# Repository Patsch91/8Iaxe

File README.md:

# 8]axe

The 8]axe is a 8-ASIC-BM1366 Miner based on the [0xaxe](https://github.com/shufps/0xaxe)

**rev1**: averaging at about 3.3-3,6TH/s with ~90 Watts on the wall on default settings (485Mhz) </br>
**rev2**: added boost converter to eliminate the extra 12V PSU / different design to fit vertain enclosures

**note**: The 8]axe is not a stand-alone device because it only supports USB. It can be run connected to a Raspberry Pi without problems. Also multiple devices can be connected to a single Pi. 

**WARNING**: The 8]Axe working with Voltage Domains is the end level boss for Pros. It's hard to get it working properly. The main reason is the powering scheme that uses 4 different voltage domain. It's difficult to get it into balance properly and needs very good and uniform cooling. The device works but can be super frustrating until it really is mining as it should. 
Therefore there is some WIP to eliminate the voltage-domains and chaining 8 Asics in one Domain instead. 
**There will be no further development in near future on this project by myself, due to another project *without* voltage-domains**
```

ASICs
=====

The 8]axe uses 8 ASICs of type BM1366

Compilation (Bootloader or CMSIS-DAP)
======================================
Start WSL on your PC and go through the followig steps:

```bash
# install curl
sudo apt install curl

# install rust
curl --proto '=https' --tlsv1.2 https://sh.rustup.rs -sSf | sh

# add to ~/.bash.rc (afterwards, opening a new terminal is needed)
echo 'source "$HOME/.cargo/env"' >> ~/.bashrc

# clone repository
git clone https://github.com/shufps/0xaxe

# clone submodules
cd 0xaxe
git submodule init
git submodule update

# add rust target for STM32L0 variants
rustup target add thumbv6m-none-eabi

# build firmware for L072
cd firmware/fw-L072KZ
./build.sh
```

## Using it on Windows running WSL

For windows the usbipd is needed to connect the device to WSL. Install it from here:

https://github.com/dorssel/usbipd-win/releases

Afterwards reboot your PC and open the `cmd` as Administrator.

Connect the USB to your PC and power on the 12V while pressing the BOOT Button to start the device in BOOT-Mode

Then:
```
C:\Windows\System32>usbipd list
Connected:
BUSID  VID:PID    DEVICE                                                        STATE
2-1    046d:c52b  Logitech USB Input Device, USB-Eingabegerät                   Not shared
3-1    0c76:161f  USB PnP Audio Device, USB-Eingabegerät                        Not shared
3-2    046d:c52b  Logitech USB Input Device, USB-Eingabegerät                   Not shared
3-3    046d:c548  Logitech USB Input Device, USB-Eingabegerät                   Not shared
4-1    8087:0aa7  Intel(R) Wireless Bluetooth(R)                                Not shared
4-2    2e8a:000c  Picoprobe CMSIS-DAP v2, Serielles USB-Gerät (COM3)            Attached
```

Note the `BUSID` for the STM32. Then

```
C:\Windows\System32> usbipd bind --busid 4-2
```

Afterwards start your WSL Linux

Then attach the device with:
```
C:\Windows\System32> usbipd attach --wsl --busid 4-2
```

When it is running you can check in your WSL-Linux if the probe is detected:
```
probe-rs list

The following debug probes were found:
[0]: Picoprobe CMSIS-DAP (VID: 2e8a, PID: 000c, Serial: E66138528337A532, CmsisDap)
```

Installation via USB Bootloader on board with `BOOT` button
===========================================================
The STM32L072CB variant has an integrated DFU Bootloader that starts when pressing the `BOOT` button during reset.

Afterwards the firmware can be flashed via `dfu-utils`:

```bash
# install cargo-binutils and llvm tools
cargo install cargo-binutils
rustup component add llvm-tools-preview

# create the firmware.bin
DEFMT_LOG=info cargo objcopy --release --bin qaxe -- -O binary 0xaxe.bin

# install dfu-utils
sudo apt-get install dfu-util

# after booting, list the devices
dfu-util --list

# flash the binary
dfu-util -a 0 -s 0x08000000:leave -D 0xaxe.bin
```

Config 
=============
Use the "config.yml.example" of the [Piaxe-Miner](https://github.com/shufps/piaxe-miner) and change it as follows:

```bash
debug_bm1366: false
verify_solo: false
miner: 0xaxe

# works only with public pool
#suggest_difficulty: 2048

0xaxe:
  name: 8]axe
  chips: 8
  fan_speed_1: 0.8
  asic_frequency: 480
  extranonce2_interval: 1.5
  serial_port_asic: "/dev/ttyACM0"
  serial_port_ctrl: "/dev/ttyACM1"

...
```

Mining Client
=============

Stratum Mining Client:<br>
https://github.com/shufps/piaxe-miner

Case
=============

I used a 80x160x170 aluminum case like this one: [Amazon](https://www.amazon.de/Aluminium-Projektbox-Mattschwarzer-DIY-Leiterplattenanschluss-W%C3%A4rmeableitungsgeh%C3%A4use-Bedienen/dp/B0CGGSVM8F/ref=sr_1_3?__mk_de_DE=%C3%85M%C3%85%C5%BD%C3%95%C3%91&crid=3NMRXLZY6ALUN&dib=eyJ2IjoiMSJ9.0MLZnspoRUt-5Sq-UXD83eHRPPewKvMh4lus8XXQpkgDJRroXYZdpFcvkPHZnSEZWGdyZPu25JsKw8C_Gw7j3U3yo7FGxp-UKuHRwNwGErpQnLGFtEGB8CJPhlUupGPSyBMCgfSQbhhh6rR9keuntOinXBiLTcwFkg9jAHzRan196B2bXwHWc_GQhccHhde_KeXf4lkzuWefDuMZS-GZUgLpMEkL2ri5-xO686sFxk3LH6hBDYjgFnlqzBNBpYp2-c1hxcX88ikJwDevu7zkgC_WFYcVderTFYBcHsyTKOc.TUGJK2RRMmqnw5Lux7s7qib6OQUQhYEMLp2vokTvp34&dib_tag=se&keywords=80x160x170+case&qid=1723150526&sprefix=80x160x170+case%2Caps%2C94&sr=8-3)

Added 2x80mm Noctua Fans to get it pretty silent 

Misc
====
If you like this project and want to support future work, feel free to donate to: (https://github.com/shufps/0xaxe)

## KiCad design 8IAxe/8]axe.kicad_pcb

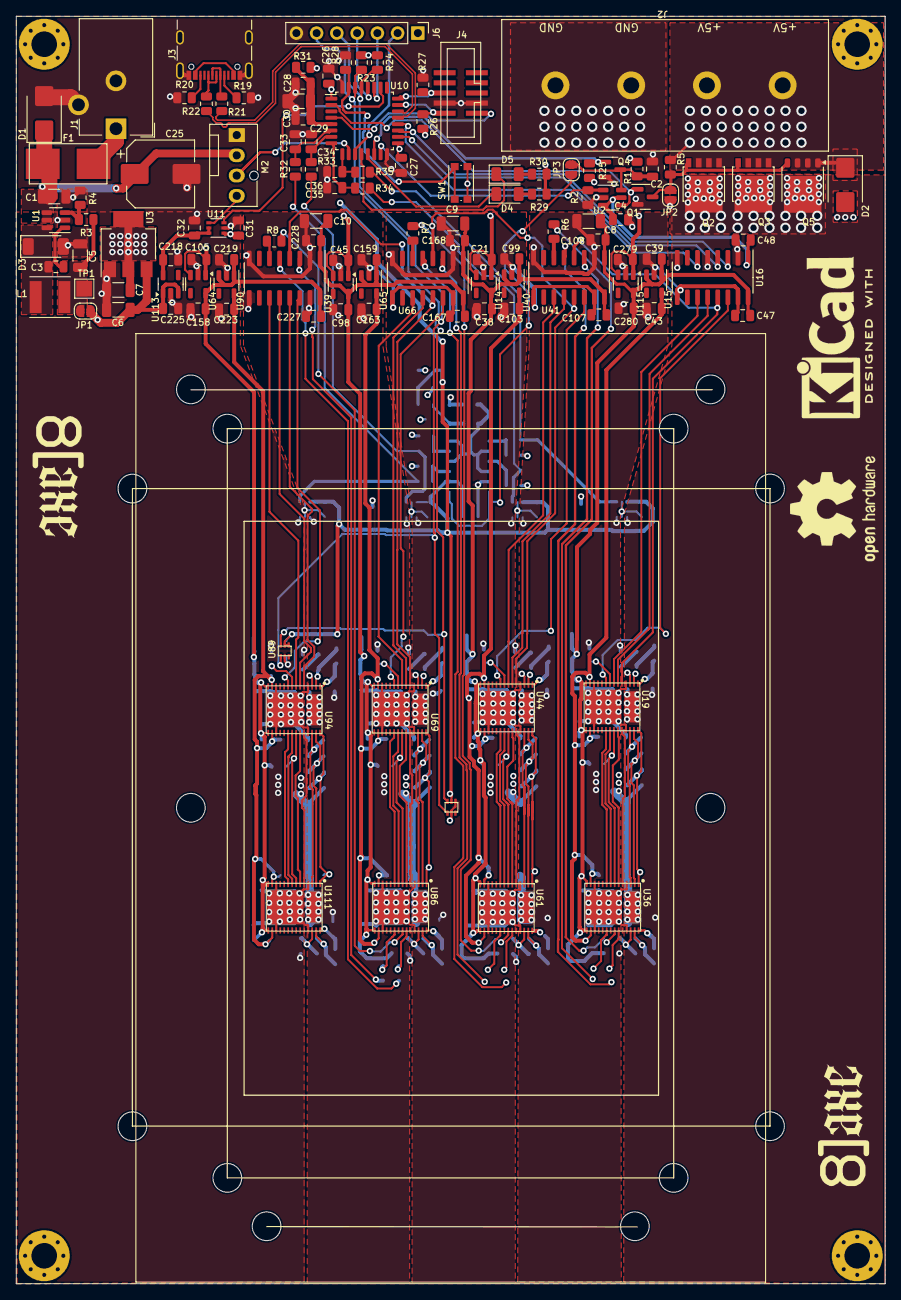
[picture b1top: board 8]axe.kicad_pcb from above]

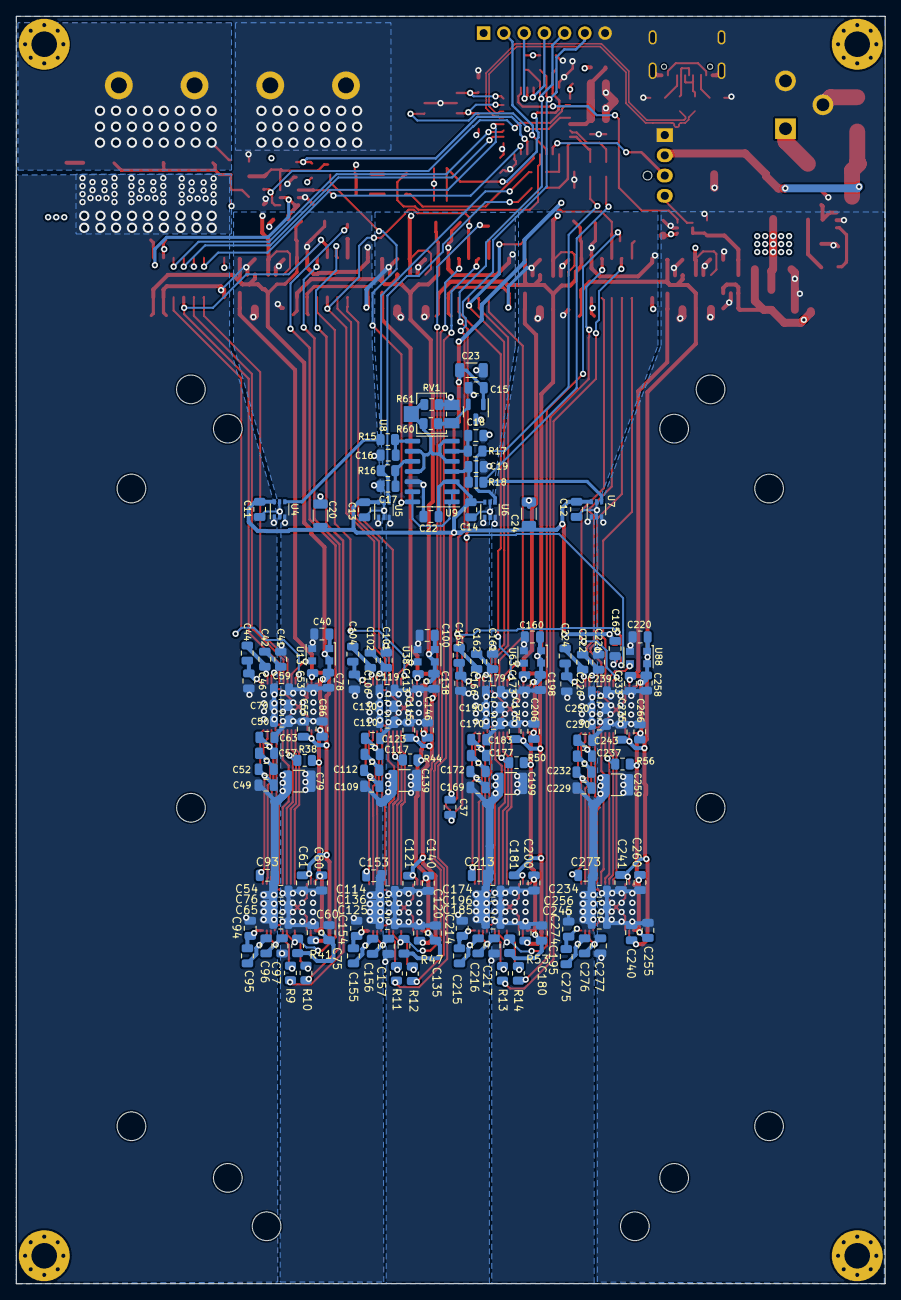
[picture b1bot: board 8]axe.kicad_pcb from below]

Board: 4 copper layers, 109.0 x 159.0 mm, 285 parts (161 on the bottom side), 164 nets.

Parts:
C1, C6, C8, C9, C10, C20, C23, C24, C30: 10µ/50V; C_1206_3216Metric
C2, C4, C11, C12, C13, C14, C15, C16, C17, C18, C19, C21, C22, C26, C27, C28, C31, C32, C33, C34, C35, C36, C37, C39, C40, C45, C47, C48, C70, C76, C99, C100, C105, C107, C108, C130, C136, C159, C160, C165, C167, C168, C190, C196, C219, C220, C227, C228, C250, C256, C279: 100n; C_0805_2012Metric
C3: 10n/250V; C_0805_2012Metric
C5, C7: 22µ/16V; C_1206_3216Metric
C25: 330µ; CP_Elec_8x10
C29, C38, C41, C42, C43, C44, C46, C49, C52, C53, C55, C57, C59, C60, C61, C63, C65, C75, C78, C80, C86, C93, C94, C95, C96, C97, C98, C101, C102, C103, C104, C106, C109, C112, C113, C115, C117, C119, C120, C121, C123, C125, C135, C138, C140, C146, C153, C154, C155, C156, C157, C158, C161, C162, C163, C164, C166, C169, C172, C173, C175, C177, C179, C180, C181, C183, C185, C195, C198, C200, C206, C213, C214, C215, C216, C217, C218, C221, C222, C223, C224, C225, C226, C229, C232, C233, C235, C237, C239, C240, C241, C243, C245, C255, C258, C260, C266, C273, C274, C275, C276, C277, C280: 1µ; C_0805_2012Metric
C50, C54, C110, C114, C170, C174, C230, C234: 10µ/16V; C_0805_2012Metric
C79, C139, C199, C259: 330µ/4V; C_1210_3225Metric
D1: SMBJ12A; D_SMB
D2: SMBJ5.0A; D_SMB
D3: PMEG4030EP,115; D_SOD-128
D4, D5: LED; LED_1206_3216Metric
F1: 0.5A; fuseholder_littlefuse_blok
J1: Barrel_Jack_Switch; BarrelJack_CUI_PJ-102AH_Horizontal
J2: Conn_01x04; BARRIER-TERMINAL-ANYTEK-4pol
J3: USB_C_Receptacle_USB2.0; USB_C_Receptacle_GCT_USB4105-xx-A_16P_TopMnt_Horizontal
J4: SWD; PinHeader_IDC_2x05_P1.27mm_Vertical_SMD
J6: Conn_01x05; PinHeader_1x07_P2.54mm_Vertical
JP1, JP2, JP3: SolderJumper_2_Open; SolderJumper-2_P1.3mm_Open_RoundedPad1.0x1.5mm
L1: 4.7µH/2A/3A; L_Taiyo-Yuden_NR-50xx
M2: Fan_4pin; FanPinHeader_1x04_P2.54mm_Vertical
Q1, Q4: BSS138; SOT-23
Q2, Q3, Q5: TPH1R712MD,L1Q; LFPAK56
R1, R2, R5, R25, R26, R27, R38, R41, R44, R47, R50, R53, R56: 10k; R_0805_2012Metric
R3: 49.9k; R_0805_2012Metric
R4: 7.15k; R_0805_2012Metric
R6, R7, R8, R9, R10, R11, R12, R13, R14, R21, R22, R31: 22; R_0805_2012Metric
R15, R16, R17, R18, R32, R33, R34, R35: 1k; R_0805_2012Metric
R19, R20: 5.1k; R_0805_2012Metric
R23, R24: 1.5k; R_0805_2012Metric
R28: 100k; R_0805_2012Metric
R29, R30: 560; R_0805_2012Metric
R60: 3.92k; R_0805_2012Metric
R61: 6.04k; R_0805_2012Metric
RV1: 10k; Potentiometer_Bourns_3214X_Vertical
SW1: boot; SW_Push_1P1T_NO_CK_KMR2
TP1: 3V3; TestPoint_Pad_2.0x2.0mm
U1: AP3211; SOT-23-6
U2: 74LVC1G175; SOT-23-6
U3: 1117-3.3; SOT-223-3_TabPin2
U4, U5, U6, U7: INA500DCK; SOT-363_SC-70-6
U8: ISL21080CIH315Z-TK; SOT-23
U9: LM339; SOIC-14_3.9x8.7mm_P1.27mm
U10: STM32L072KZT6; LQFP-32_7x7mm_P0.8mm
U11: TXU0101; SOT-363_SC-70-6
U12, U89: TMP1075; TMP1075-DRL
U13, U38, U63, U88: 25MHz; Oscillator_SMD_EuroQuartz_XO32-4Pin_3.2x2.5mm
U14, U39, U64, U115: MCP1824T-1802E; SOT-23-5
U15, U40, U65, U90: NCP114ASN080T1G; SOT-23-5
U16, U41, U66, U91: ADUM141E0BRZ-RL7; SOIC-16_3.9x9.9mm_P1.27mm
U19, U36, U44, U61, U69, U86, U94, U111: BM1366_mode1; BM1366
U113: NCP718xSN500; SOT-23-5

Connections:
+0V8_0: C43.1, C53.2, C55.2, C60.2, C61.2, U15.5 (OUT), U19.13 (VDDIO_08_0), U19.16 (VDDIO_08_1), U36.13 (VDDIO_08_0), U36.16 (VDDIO_08_1)
+0V8_1: C103.1, C113.2, C115.2, C120.2, C121.2, U40.5 (OUT), U44.13 (VDDIO_08_0), U44.16 (VDDIO_08_1), U61.13 (VDDIO_08_0), U61.16 (VDDIO_08_1)
+0V8_2: C163.1, C173.2, C175.2, C180.2, C181.2, U65.5 (OUT), U69.13 (VDDIO_08_0), U69.16 (VDDIO_08_1), U86.13 (VDDIO_08_0), U86.16 (VDDIO_08_1)
+0V8_3: C223.1, C233.2, C235.2, C240.2, C241.2, U90.5 (OUT), U94.13 (VDDIO_08_0), U94.16 (VDDIO_08_1), U111.13 (VDDIO_08_0), U111.16 (VDDIO_08_1)
+1V8_0: C8.1, C39.1, C40.1, C47.1, C75.1, C78.1, C80.1, C86.1, C108.1, C280.1, R38.2, R41.2, U13.1 (Standby), U13.4 (VDD), U15.1 (IN), U15.3 (EN), U16.16 (VDD2), U19.14 (VDDIO_18_0), U19.15 (VDDIO_18_1), U36.14 (VDDIO_18_0), U36.15 (VDDIO_18_1), U41.1 (VDD1), U115.5 (VOUT)
+1V8_1: C9.1, C38.1, C99.1, C100.1, C107.1, C135.1, C138.1, C140.1, C146.1, C168.1, R44.2, R47.2, U14.5 (VOUT), U38.1 (Standby), U38.4 (VDD), U40.1 (IN), U40.3 (EN), U41.16 (VDD2), U44.14 (VDDIO_18_0), U44.15 (VDDIO_18_1), U61.14 (VDDIO_18_0), U61.15 (VDDIO_18_1), U66.1 (VDD1)
+1V8_2: C10.1, C98.1, C159.1, C160.1, C167.1, C195.1, C198.1, C200.1, C206.1, C228.1, R50.2, R53.2, U39.5 (VOUT), U63.1 (Standby), U63.4 (VDD), U65.1 (IN), U65.3 (EN), U66.16 (VDD2), U69.14 (VDDIO_18_0), U69.15 (VDDIO_18_1), U86.14 (VDDIO_18_0), U86.15 (VDDIO_18_1), U91.1 (VDD1)
+1V8_3: C158.1, C219.1, C220.1, C227.1, C255.1, C258.1, C260.1, C266.1, R56.2, U64.5 (VOUT), U88.1 (Standby), U88.4 (VDD), U90.1 (IN), U90.3 (EN), U91.16 (VDD2), U94.14 (VDDIO_18_0), U94.15 (VDDIO_18_1), U111.14 (VDDIO_18_0), U111.15 (VDDIO_18_1)
+3V3: C4.1, C7.1, C11.1, C12.1, C13.1, C14.1, C15.1, C20.1, C22.1, C23.1, C24.1, C26.1, C27.1, C31.1, C37.1, C48.1, C165.1, J6.1, R1.2, R23.1, R24.1, R25.2, R26.2, R29.1, R30.1, R31.2, SW1.2, U2.3 (D), U2.5 (VCC), U3.2 (VO), U4.6 (V+), U5.6 (V+), U6.6 (V+), U7.6 (V+), U8.1 (Vin), U9.3 (V+), U10.1 (VDD), U10.17 (VDD), U11.1 (VCCA), U12.5 (V+), U16.1 (VDD1), U89.4 (A0), U89.5 (V+)
+3V3A: C28.1, C29.1, C30.1, R31.1, U10.5 (VDDA)
+5V: C32.1, C218.1, U11.5 (OE), U11.6 (VCCB), U113.5 (OUT)
+5V_PWR: C46.2, C49.1, C50.1, C54.1, C59.1, C65.1, C70.1, C76.1, C79.1, C93.2, C94.1, Q2.5 (D), Q3.5 (D), Q5.5 (D), U4.1 (IN+), U19.29 (VDD), U36.29 (VDD)
+5V_PWR_EXT: D2.1 (A1), J2.1, J2.2, Q2.1 (S), Q2.2 (S), Q2.3 (S), Q3.1 (S), Q3.2 (S), Q3.3 (S), Q5.1 (S), Q5.2 (S), Q5.3 (S), R5.2
+6.5V: C6.1, C21.1, C45.1, C105.1, C225.1, C279.1, JP1.2 (B), U3.3 (VI), U14.1 (VIN), U14.3 (EN), U39.1 (VIN), U39.3 (EN), U64.1 (VIN), U64.3 (EN), U113.1 (IN), U113.3 (EN), U115.1 (VIN), U115.3 (EN)
+12V: C1.1, C25.1, D1.1 (A1), F1.1, M2.2 (+), U1.4 (EN), U1.5 (IN)
/Power/PWR_EN: R2.2, U2.1 (C), U10.15 (PB1)
/Power/Q: Q1.1 (G), U2.4 (Q), U10.2 (PC14)
/Power/SHUTDOWN: C2.1, JP3.2 (B), Q4.3 (D), R1.1, U2.6 (~CLR)
/flex/2.5V: R60.1, RV1.1, U8.2 (Vout)
/flex/BO_0: R9.2, U41.5 (VIC)
/flex/BO_1: R11.2, U66.5 (VIC)
/flex/BO_2: R13.2, U91.5 (VIC)
/flex/CO_0: R10.2, U41.3 (VIA)
/flex/CO_1: R12.2, U66.3 (VIA)
/flex/CO_2: R14.2, U91.3 (VIA)
/flex/NRSTO_0: U16.13 (VOB), U19.5 (NRSTI), U41.4 (VIB)
/flex/NRSTO_1: U41.13 (VOB), U44.5 (NRSTO), U66.4 (VIB)
/flex/NRSTO_2: U66.13 (VOB), U69.5 (NRSTI), U91.4 (VIB)
/flex/RESET: U10.18 (PA8), U16.4 (VIB)
/flex/RI_0: R6.1, R41.1, U36.22 (RI)
/flex/RI_1: R7.1, R47.1, U61.22 (RI)
/flex/RI_2: R8.1, R53.1, U86.22 (RI)
/flex/RXD: U10.20 (PA10), U16.6 (VOD)
/flex/TXD: U10.19 (PA9), U16.3 (VIA)
/flex/V_FLEX1: R15.1, R35.2, U4.4 (OUT)
/flex/V_FLEX2: R16.1, R34.2, U5.4 (OUT)
/flex/V_FLEX3: R17.1, R33.2, U6.4 (OUT)
/flex/V_FLEX4: R18.1, R32.2, U7.4 (OUT)
/flex/flex1/BO: R9.1, U36.23 (BO)
/flex/flex1/CLKI: U13.3 (Out), U19.8 (CLKI)
/flex/flex1/CO: R10.1, U36.20 (CO)
/flex/flex1/I_BI: U16.12 (VOC), U19.6 (BI)
/flex/flex1/I_CI: U16.14 (VOA), U19.9 (CI)
/flex/flex1/I_RO: U16.11 (VID), U19.7 (RO)
/flex/flex2/BO: R11.1, U61.23 (BO)
/flex/flex2/CLKI: U38.3 (Out), U44.8 (CLKO)
/flex/flex2/CO: R12.1, U61.20 (CO)
/flex/flex2/I_BI: U41.12 (VOC), U44.6 (BO)
/flex/flex2/I_CI: U41.14 (VOA), U44.9 (CO)
/flex/flex2/I_RO: U41.11 (VID), U44.7 (RI)
/flex/flex2/RO: R6.2, U41.6 (VOD)
/flex/flex3/BO: R13.1, U86.23 (BO)
/flex/flex3/CLKI: U63.3 (Out), U69.8 (CLKI)
/flex/flex3/CO: R14.1, U86.20 (CO)
/flex/flex3/I_BI: U66.12 (VOC), U69.6 (BI)
/flex/flex3/I_CI: U66.14 (VOA), U69.9 (CI)
/flex/flex3/I_RO: U66.11 (VID), U69.7 (RO)
/flex/flex3/RO: R7.2, U66.6 (VOD)
/flex/flex4/CLKI: U88.3 (Out), U94.8 (CLKI)
/flex/flex4/I_BI: U91.12 (VOC), U94.6 (BI)
/flex/flex4/I_CI: U91.14 (VOA), U94.9 (CI)
/flex/flex4/I_NRSTI: U91.13 (VOB), U94.5 (NRSTI)
/flex/flex4/I_RO: U91.11 (VID), U94.7 (RO)
/flex/flex4/RO: R8.2, U91.6 (VOD)
/stm32/LED1: D5.1 (K), U10.12 (PA6)
/stm32/LED2: D4.1 (K), U10.13 (PA7)
/stm32/NRST: J4.1, U10.4 (NRST)
/stm32/PWM_3V3: U10.26 (PB3), U11.3 (A)
/stm32/PWM_3V3_EXT: J6.2, U10.11 (PA5)
/stm32/SCL: J6.5, R24.2, U10.29 (PB6), U12.1 (SCL), U89.1 (SCL)
/stm32/SDA: J6.6, R23.2, U10.30 (PB7), U12.6 (SDA), U89.6 (SDA)
/stm32/SPARE1: J6.3, U10.27 (PB4)
/stm32/SPARE2: J6.4, U10.28 (PB5)
/stm32/SWCLK: J4.6, R27.2, U10.24 (PA14)
/stm32/SWDIO: J4.2, R26.1, U10.23 (PA13)
/stm32/TACHO: M2.3 (Tacho), U10.10 (PA4)
/stm32/USB_D+: R22.1, U10.22 (PA12)
/stm32/USB_D-: R21.1, U10.21 (PA11)
/stm32/X: J3.A4 (VBUS), J3.A9 (VBUS), J3.B4 (VBUS), J3.B9 (VBUS)
GND: C1.2, C2.2, C4.2, C5.2, C6.2, C7.2, C11.2, C12.2, C13.2, C14.2, C15.2, C16.2, C17.2, C18.2, C19.2, C20.2, C22.2, C23.2, C24.2, C25.2, C26.2, C27.2, C28.2, C29.2, C30.2, C31.2, C32.2, C33.2, C34.2, C35.2, C36.2, C37.2, C48.2, C105.2, C158.2, C165.2, C218.2, C219.2, C220.2, C221.1, C223.2, C225.2, C227.2, C230.2, C233.1, C234.2, C235.1, C239.2, C240.1, C241.1, C243.2, C245.2, C250.2, C255.2, C256.2, C258.2, C259.2, C260.2, C266.2, C277.2, D1.2 (A2), D2.2 (A2), D3.2 (A), J1.2, J1.3, J2.3, J2.4, J3.A1 (GND), J3.A12 (GND), J3.B1 (GND), J3.B12 (GND), J3.S1 (SHIELD), J4.3, J4.4, J6.7, JP2.1 (A), M2.1 (-), Q1.2 (S), Q4.2 (S), R2.1, R4.2, R19.1, R20.1, R27.1, R28.1, R61.2, RV1.3, U1.2 (GND), U2.2 (GND), U3.1 (GND), U4.2 (V-), U4.5 (REF), U5.2 (V-), U5.5 (REF), U6.2 (V-), U6.5 (REF), U7.2 (V-), U7.3 (IN-), U7.5 (REF), U8.3 (GND), U9.12 (V-), U10.16 (VSS), U10.32 (VSS), U11.2 (GND), U12.2 (GND), U12.4 (A0), U16.2 (GND1), U16.5 (VIC), U16.8 (GND1), U64.2 (GND), U88.2 (GND), U89.2 (GND), U90.2 (GND), U91.9 (GND2), U91.15 (GND2), U94.4 (VSS), U94.12 (PLL_VSS), U94.17 (VSS), U94.25 (VSS), U94.30 (GND), U111.4 (VSS), U111.12 (PLL_VSS), U111.17 (VSS), U111.25 (VSS), U111.30 (GND), U113.2 (GND)
unnamed: C3.2, D3.1 (K), L1.1, U1.6 (SW)
unnamed: D4.2 (A), R29.2
unnamed: D5.2 (A), R30.2
unnamed: F1.2, J1.1
unnamed: J3.A5 (CC1), R19.2
unnamed: J3.B5 (CC2), R20.2
unnamed: J3.A6 (D+), J3.B6 (D+), R22.2
unnamed: J3.A7 (D-), J3.B7 (D-), R21.2
unnamed: C5.1, JP1.1 (A), L1.2, R3.1, TP1.1
unnamed: JP2.2 (B), Q1.3 (D), Q2.4 (G), Q3.4 (G), Q5.4 (G), R5.1
unnamed: JP3.1 (A), U9.1, U9.2, U9.13, U9.14
unnamed: M2.4 (PWM), U11.4 (BY)
unnamed: Q4.1 (G), R25.1, U10.14 (PB0)
unnamed: C3.1, U1.1 (BS)
unnamed: R3.2, R4.1, U1.3 (FB)
unnamed: R60.2, R61.1, RV1.2, U9.5 (+), U9.7 (+), U9.9 (+), U9.11 (+)
unnamed: C19.1, R18.2, U9.4 (-)
unnamed: C18.1, R17.2, U9.6 (-)
unnamed: C17.1, R16.2, U9.10 (-)
unnamed: C16.1, R15.2, U9.8 (-)
unnamed: R28.2, SW1.1, U10.31 (BOOT0)
unnamed: C33.1, R32.1, U10.6 (PA0)
unnamed: C34.1, R33.1, U10.7 (PA1)
unnamed: C35.1, R34.1, U10.8 (PA2)
unnamed: C36.1, R35.1, U10.9 (PA3)
unnamed: U19.23 (BO), U36.6 (BI)
unnamed: U19.21 (CLKO), U36.8 (CLKI)
unnamed: U19.20 (CO), U36.9 (CI)
unnamed: U19.24 (NRSTO), U36.5 (NRSTI)
unnamed: R38.1, U19.22 (RI), U36.7 (RO)
unnamed: C44.2, C46.1, U19.1 (VDD1_0)
unnamed: C49.2, C52.2, C93.1, U19.28 (VDD1_1), U36.1 (VDD1_0)
unnamed: C42.2, C44.1, U19.2 (VDD2_0)
unnamed: C52.1, C57.1, U19.27 (VDD2_1), U36.2 (VDD2_0)
unnamed: C41.2, C42.1, U19.3 (VDD3_0)
unnamed: C57.2, C63.1, U19.26 (VDD3_1), U36.3 (VDD3_0)
unnamed: C94.2, C95.1, U36.28 (VDD1_1)
unnamed: C95.2, C96.1, U36.27 (VDD2_1)
unnamed: C96.2, C97.1, U36.26 (VDD3_1)
unnamed: U44.23 (BI), U61.6 (BI)
unnamed: U44.20 (CI), U61.9 (CI)
unnamed: U44.21 (CLKI), U61.8 (CLKI)
unnamed: U44.24 (NRSTI), U61.5 (NRSTI)
unnamed: R44.1, U44.22 (RO), U61.7 (RO)
unnamed: C104.2, C106.1, U44.1 (VDD1_0)
unnamed: C109.2, C112.2, C153.1, U44.28 (VDD1_1), U61.1 (VDD1_0)
unnamed: C102.2, C104.1, U44.2 (VDD2_0)
unnamed: C112.1, C117.1, U44.27 (VDD2_1), U61.2 (VDD2_0)
unnamed: C101.2, C102.1, U44.3 (VDD3_0)
unnamed: C117.2, C123.1, U44.26 (VDD3_1), U61.3 (VDD3_0)
unnamed: C154.2, C155.1, U61.28 (VDD1_1)
unnamed: C155.2, C156.1, U61.27 (VDD2_1)
unnamed: C156.2, C157.1, U61.26 (VDD3_1)
unnamed: U69.23 (BO), U86.6 (BI)
unnamed: U69.21 (CLKO), U86.8 (CLKI)
unnamed: U69.20 (CO), U86.9 (CI)
unnamed: U69.24 (NRSTO), U86.5 (NRSTI)
unnamed: R50.1, U69.22 (RI), U86.7 (RO)
unnamed: C164.2, C166.1, U69.1 (VDD1_0)
unnamed: C169.2, C172.2, C213.1, U69.28 (VDD1_1), U86.1 (VDD1_0)
unnamed: C162.2, C164.1, U69.2 (VDD2_0)
unnamed: C172.1, C177.1, U69.27 (VDD2_1), U86.2 (VDD2_0)
unnamed: C161.2, C162.1, U69.3 (VDD3_0)
unnamed: C177.2, C183.1, U69.26 (VDD3_1), U86.3 (VDD3_0)
unnamed: C214.2, C215.1, U86.28 (VDD1_1)
unnamed: C215.2, C216.1, U86.27 (VDD2_1)
unnamed: C216.2, C217.1, U86.26 (VDD3_1)
unnamed: C224.2, C226.1, U94.1 (VDD1_0)
unnamed: C222.2, C224.1, U94.2 (VDD2_0)
unnamed: C221.2, C222.1, U94.3 (VDD3_0)
unnamed: U94.23 (BO), U111.6 (BI)
unnamed: U94.20 (CO), U111.9 (CI)
unnamed: U94.21 (CLKO), U111.8 (CLKI)
unnamed: U94.24 (NRSTO), U111.5 (NRSTI)
unnamed: R56.1, U94.22 (RI), U111.7 (RO)
unnamed: C229.2, C232.2, C273.1, U94.28 (VDD1_1), U111.1 (VDD1_0)
unnamed: C274.2, C275.1, U111.28 (VDD1_1)
unnamed: C232.1, C237.1, U94.27 (VDD2_1), U111.2 (VDD2_0)
unnamed: C275.2, C276.1, U111.27 (VDD2_1)
unnamed: C237.2, C243.1, U94.26 (VDD3_1), U111.3 (VDD3_0)
unnamed: C276.2, C277.1, U111.26 (VDD3_1)
V1_G0: C8.2, C39.2, C40.2, C41.1, C43.2, C47.2, C50.2, C53.1, C54.2, C55.1, C59.2, C60.1, C61.1, C63.2, C65.2, C70.2, C75.2, C76.2, C78.2, C79.2, C80.2, C86.2, C97.2, C106.2, C108.2, C109.1, C110.1, C114.1, C119.1, C125.1, C130.1, C136.1, C139.1, C153.2, C154.1, C279.2, C280.2, U4.3 (IN-), U5.1 (IN+), U13.2 (GND), U15.2 (GND), U16.9 (GND2), U16.15 (GND2), U19.4 (VSS), U19.12 (PLL_VSS), U19.17 (VSS), U19.25 (VSS), U19.30 (GND), U36.4 (VSS), U36.12 (PLL_VSS), U36.17 (VSS), U36.25 (VSS), U36.30 (GND), U41.2 (GND1), U41.8 (GND1), U44.29 (VDD), U61.29 (VDD), U115.2 (GND)
V2_G1: C9.2, C21.2, C38.2, C99.2, C100.2, C101.1, C103.2, C107.2, C110.2, C113.1, C114.2, C115.1, C119.2, C120.1, C121.1, C123.2, C125.2, C130.2, C135.2, C136.2, C138.2, C139.2, C140.2, C146.2, C157.2, C166.2, C168.2, C169.1, C170.1, C174.1, C179.1, C185.1, C190.1, C196.1, C199.1, C213.2, C214.1, U5.3 (IN-), U6.1 (IN+), U14.2 (GND), U38.2 (GND), U40.2 (GND), U41.9 (GND2), U41.15 (GND2), U44.4 (VSS), U44.12 (PLL_VSS), U44.17 (VSS), U44.25 (VSS), U44.30 (GND), U61.4 (VSS), U61.12 (PLL_VSS), U61.17 (VSS), U61.25 (VSS), U61.30 (GND), U66.2 (GND1), U66.8 (GND1), U69.29 (VDD), U86.29 (VDD)
V3_G2: C10.2, C45.2, C98.2, C159.2, C160.2, C161.1, C163.2, C167.2, C170.2, C173.1, C174.2, C175.1, C179.2, C180.1, C181.1, C183.2, C185.2, C190.2, C195.2, C196.2, C198.2, C199.2, C200.2, C206.2, C217.2, C226.2, C228.2, C229.1, C230.1, C234.1, C239.1, C245.1, C250.1, C256.1, C259.1, C273.2, C274.1, U6.3 (IN-), U7.1 (IN+), U39.2 (GND), U63.2 (GND), U65.2 (GND), U66.9 (GND2), U66.15 (GND2), U69.4 (VSS), U69.12 (PLL_VSS), U69.17 (VSS), U69.25 (VSS), U69.30 (GND), U86.4 (VSS), U86.12 (PLL_VSS), U86.17 (VSS), U86.25 (VSS), U86.30 (GND), U91.2 (GND1), U91.8 (GND1), U94.29 (VDD), U111.29 (VDD)
